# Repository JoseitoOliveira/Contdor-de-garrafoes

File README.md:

# Contdor de garrafões
 Contador de garrafoes e controlador de esteira industrial.

## Requisitos:
- Arduino_FreeRTOS.h
- Bounce2.h
- Keypad.h
- LiquidCrystal.h

## Imagens
### 3º layout

### 2º layout

### 1º layout

### 1º montagem em protoboard

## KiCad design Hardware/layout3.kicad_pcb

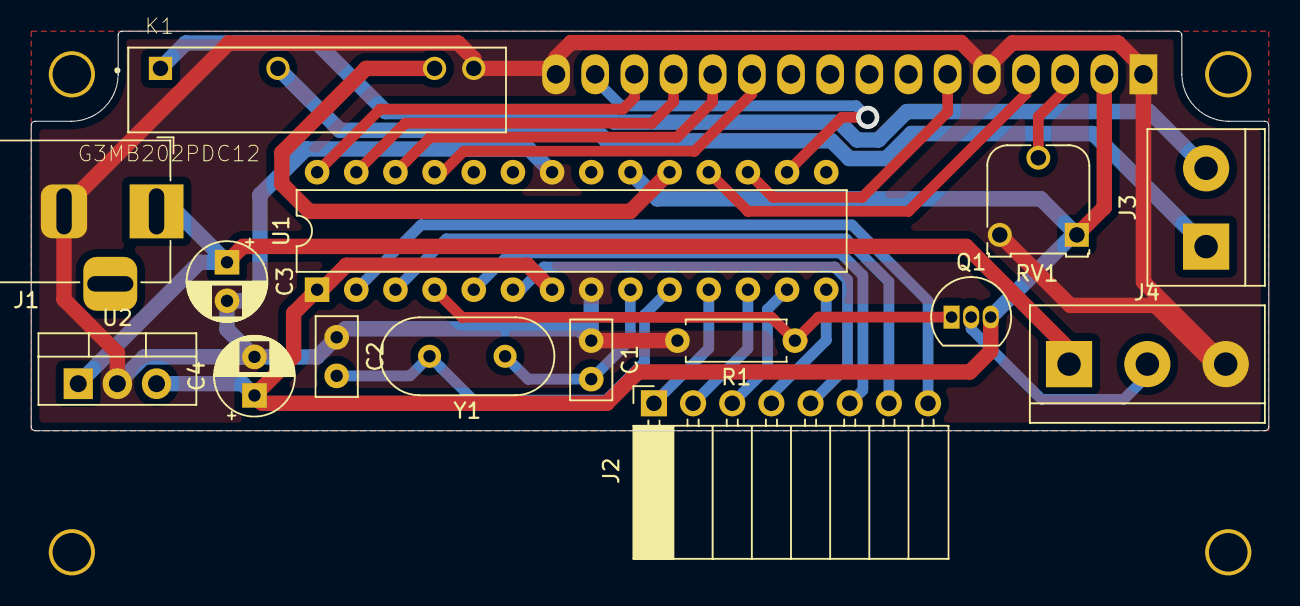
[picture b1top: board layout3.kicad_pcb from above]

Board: 2 copper layers, 80.3 x 25.9 mm, 16 parts (1 on the bottom side), 26 nets.

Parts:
C1, C2: C; C_Disc_D5.0mm_W2.5mm_P2.50mm
C3, C4: C; CP_Radial_D5.0mm_P2.50mm
DS1: RC1602A; WC1602A
J1: Jack-DC; BarrelJack_Horizontal
J2: Teclado matricial; PinSocket_1x08_P2.54mm_Horizontal
J3: Conn_01x02; TerminalBlock_bornier-2_P5.08mm
J4: Conn_01x03; TerminalBlock_bornier-3_P5.08mm
K1: G3MB202PDC12; RELAY_G3MB202PDC12
Q1: 2N7000; TO-92_Inline
R1: R; R_Axial_DIN0207_L6.3mm_D2.5mm_P7.62mm_Horizontal
RV1: R_POT; Potentiometer_Runtron_RM-065_Vertical
U1: ATmega328-PU; DIP-28_W7.62mm
U2: LM7805_TO220; TO-220-3_Vertical
Y1: Crystal; Crystal_HC18-U_Vertical

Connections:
GND: C1.1, C2.1, C3.2, C4.2, DS1.1, DS1.5, DS1.16, J1.2, J4.3, K1.4, R1.2, RV1.3, U1.8, U1.22, U2.2
LCD_A: DS1.15, U1.16
unnamed: C1.2, U1.9, Y1.1
unnamed: C2.2, U1.10, Y1.2
unnamed: DS1.3, RV1.2
unnamed: J3.1, K1.2
unnamed: J3.2, K1.1
unnamed: J4.2, Q1.2
Pino_2_int: Q1.1, R1.1, U1.4
Pino_3: J2.8, U1.2
Pino_4: J2.7, U1.3
Pino_5: J2.6, U1.5
Pino_6: J2.5, U1.6
Pino_7: J2.4, U1.14
Pino_8: J2.3, U1.13
Pino_9: J2.2, U1.12
Pino_10: J2.1, U1.11
Pino_11: DS1.6, U1.17
Pino_12: DS1.4, U1.18
Pino_13: K1.3, U1.19
Pino_16_A2: DS1.11, U1.25
Pino_17_A3: DS1.12, U1.26
Pino_18_A4: DS1.13, U1.27
Pino_19_A5: DS1.14, U1.28
vcc: C4.1, DS1.2, Q1.3, RV1.1, U1.1, U1.7, U1.20, U2.3
vcc_12v: C3.1, J1.1, J4.1, U2.1

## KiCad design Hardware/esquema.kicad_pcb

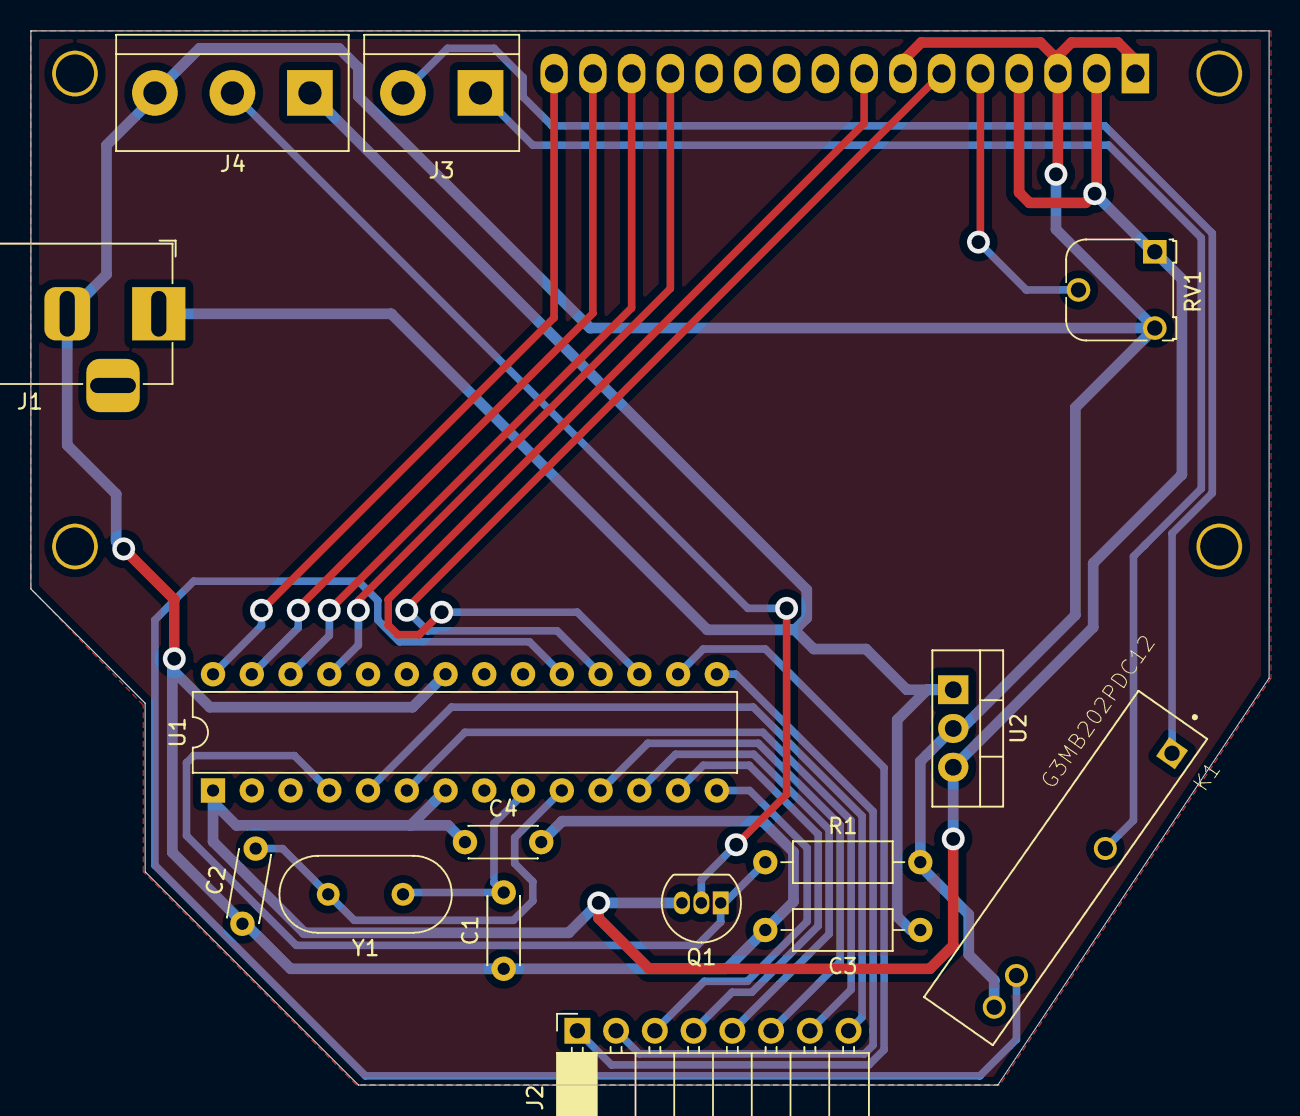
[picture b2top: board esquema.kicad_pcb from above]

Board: 2 copper layers, 81.2 x 69.1 mm, 16 parts (1 on the bottom side), 25 nets.

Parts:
C1, C2, C4: C; C_Disc_D4.3mm_W1.9mm_P5.00mm
C3: C; R_Axial_DIN0207_L6.3mm_D2.5mm_P10.16mm_Horizontal
DS1: HY1602E; WC1602A
J1: Jack-DC; BarrelJack_Horizontal
J2: Teclado matricial; PinSocket_1x08_P2.54mm_Horizontal
J3: Conn_01x02; TerminalBlock_bornier-2_P5.08mm
J4: Conn_01x03; TerminalBlock_bornier-3_P5.08mm
K1: G3MB202PDC12; RELAY_G3MB202PDC12
Q1: 2N7000; TO-92_Inline
R1: R; R_Axial_DIN0207_L6.3mm_D2.5mm_P10.16mm_Horizontal
RV1: R_POT; Potentiometer_Runtron_RM-065_Vertical
U1: ATmega328-PU; DIP-28_W7.62mm
U2: LM7805_TO220; TO-220-3_Vertical
Y1: Crystal; Crystal_HC18-U_Vertical

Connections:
GND: C1.1, C2.1, C3.2, C4.2, DS1.1, DS1.3, DS1.7, J1.2, J4.3, K1.4, R1.2, RV1.3, U1.8, U1.22, U2.2
unnamed: C1.2, U1.9, Y1.1
unnamed: C2.2, U1.10, Y1.2
unnamed: DS1.5, RV1.2
unnamed: J3.1, K1.2
unnamed: J3.2, K1.1
unnamed: J4.2, Q1.2
Pino_2_int: Q1.1, R1.1, U1.4
Pino_3: J2.8, U1.5
Pino_4: J2.7, U1.6
Pino_5: J2.6, U1.11
Pino_6: J2.5, U1.12
Pino_7: J2.4, U1.13
Pino_8: J2.3, U1.14
Pino_9: J2.2, U1.15
Pino_10: J2.1, U1.16
Pino_11: DS1.8, U1.17
Pino_12: DS1.6, U1.18
Pino_13: K1.3, U1.19
Pino_16_A2: DS1.13, U1.25
Pino_17_A3: DS1.14, U1.26
Pino_18_A4: DS1.15, U1.27
Pino_19_A5: DS1.16, U1.28
vcc: C4.1, DS1.2, DS1.4, Q1.3, RV1.1, U1.1, U1.7, U1.20, U2.3
vcc_12v: C3.1, J1.1, J4.1, U2.1

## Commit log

2021-02-19 Commit Inicial
2021-04-03 Atualização
2021-04-03 imagens do novo layout
2021-04-03 add images
